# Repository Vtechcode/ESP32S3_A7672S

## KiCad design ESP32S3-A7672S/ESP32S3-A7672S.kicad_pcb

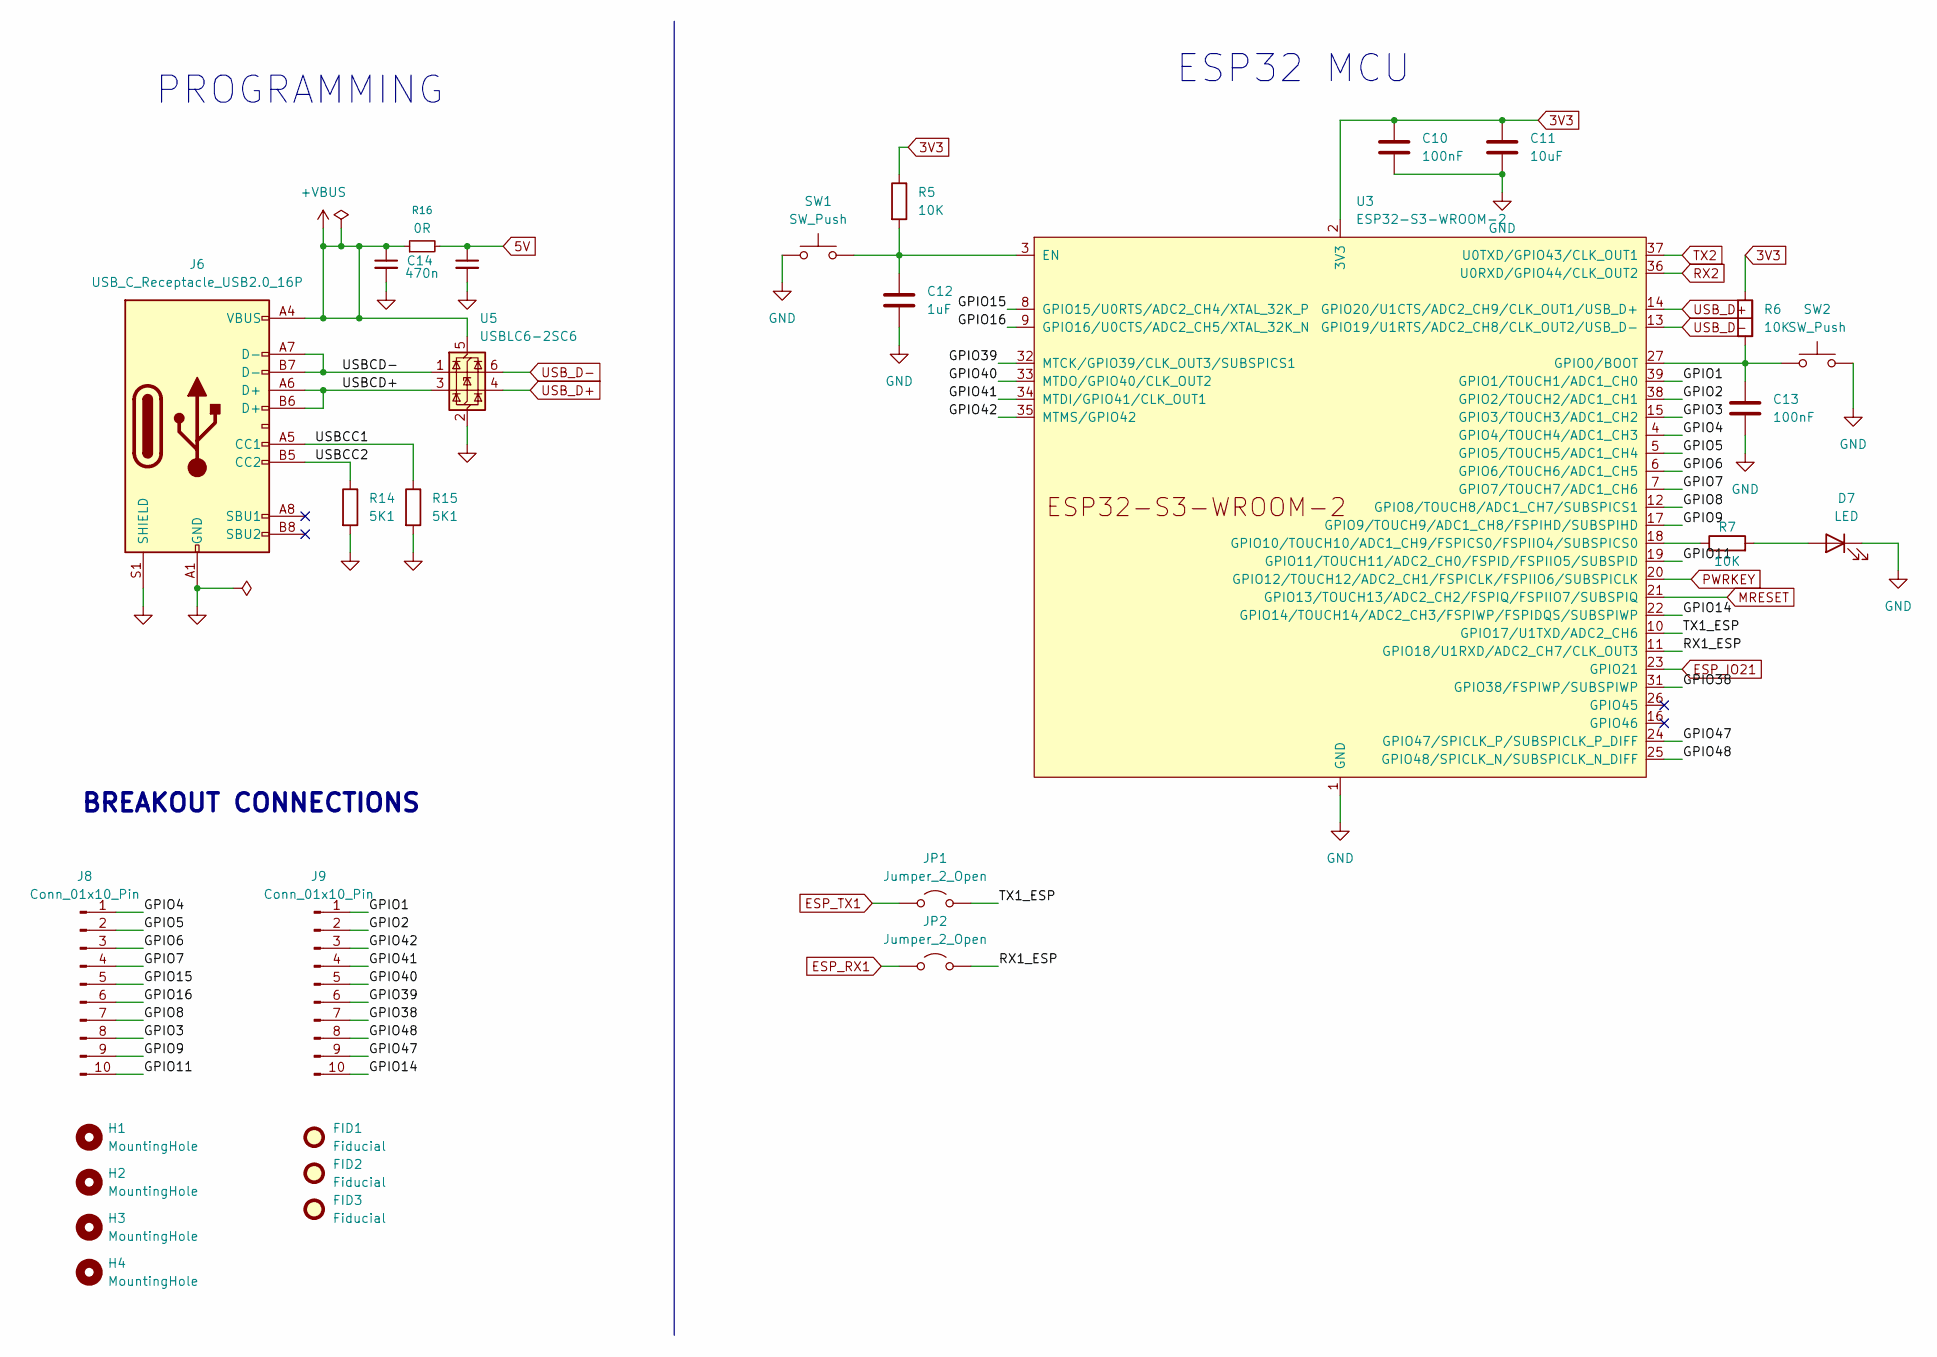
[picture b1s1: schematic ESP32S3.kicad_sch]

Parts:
C10, C13: 100nF; C_0603_1608Metric_Pad1.08x0.95mm_HandSolder; LCSC number C16194197
C11: 10uF; C_0603_1608Metric_Pad1.08x0.95mm_HandSolder; LCSC number C194427
C12: 1uF; C_0603_1608Metric_Pad1.08x0.95mm_HandSolder; LCSC number C29936
C14, C15: 470n; C_0402_1005Metric; LCSC number C364319
D7: LED; LED_0805_2012Metric_Pad1.15x1.40mm_HandSolder; LCSC number C5879383
FID1, FID2, FID3: Fiducial; Fiducial_0.5mm_Mask1.5mm
H1, H2, H3, H4: MountingHole; MountingHole_3.2mm_M3
J6: USB_C_Receptacle_USB2.0_16P; USB_C_Receptacle_GCT_USB4105-xx-A_16P_TopMnt_Horizontal; LCSC number C45082766
J8, J9: Conn_01x10_Pin; PinSocket_1x10_P2.54mm_Vertical
JP1, JP2: Jumper_2_Open; TestPoint_2Pads_Pitch2.54mm_Drill0.8mm
R5, R6, R7: 10K; R_0603_1608Metric_Pad0.98x0.95mm_HandSolder; LCSC number C2479067
R14: 5K1; R_0603_1608Metric_Pad0.98x0.95mm_HandSolder; LCSC number C123727
R15: 5K1; R_0402_1005Metric; LCSC number C123727
R16: 0R; R_0603_1608Metric; LCSC number C100044
SW1, SW2: SW_Push; SW_PUSH_6mm; LCSC number C428628
U3: ESP32-S3-WROOM-2; LCSC number C42417293
U5: USBLC6-2SC6; SOT-23-6; LCSC number C7519

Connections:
3V3: C10.1, C11.1, R5.1, R6.1, U3.2 (3V3); also elsewhere on the board
5V: C15.1, R16.2; also elsewhere on the board
+VBUS: C14.1, J6.A4 (VBUS), J6.A9 (VBUS), J6.B4 (VBUS), J6.B9 (VBUS), R16.1, U5.5 (VBUS)
/ESP32S3/GPIO1: J9.1, U3.39 (GPIO1/TOUCH1/ADC1_CH0)
/ESP32S3/GPIO2: J9.2, U3.38 (GPIO2/TOUCH2/ADC1_CH1)
/ESP32S3/GPIO3: J8.8, U3.15 (GPIO3/TOUCH3/ADC1_CH2)
/ESP32S3/GPIO4: J8.1, U3.4 (GPIO4/TOUCH4/ADC1_CH3)
/ESP32S3/GPIO5: J8.2, U3.5 (GPIO5/TOUCH5/ADC1_CH4)
/ESP32S3/GPIO6: J8.3, U3.6 (GPIO6/TOUCH6/ADC1_CH5)
/ESP32S3/GPIO7: J8.4, U3.7 (GPIO7/TOUCH7/ADC1_CH6)
/ESP32S3/GPIO8: J8.7, U3.12 (GPIO8/TOUCH8/ADC1_CH7/SUBSPICS1)
/ESP32S3/GPIO9: J8.9, U3.17 (GPIO9/TOUCH9/ADC1_CH8/FSPIHD/SUBSPIHD)
/ESP32S3/GPIO11: J8.10, U3.19 (GPIO11/TOUCH11/ADC2_CH0/FSPID/FSPIIO5/S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)
/ESP32S3/GPIO14: J9.10, U3.22 (GPIO14/TOUCH14/ADC2_CH3/FSPIWP/FSPIDQS/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)
/ESP32S3/GPIO15: J8.5, U3.8 (GPIO15/U0RTS/ADC2_CH4/XTAL_32K_P)
/ESP32S3/GPIO16: J8.6, U3.9 (GPIO16/U0CTS/ADC2_CH5/XTAL_32K_N)
/ESP32S3/GPIO38: J9.7, U3.31 (GPIO38/FSPIWP/SUBSPIWP)
/ESP32S3/GPIO39: J9.6, U3.32 (MTCK/GPIO39/CLK_OUT3/SUBSPICS1)
/ESP32S3/GPIO40: J9.5, U3.33 (MTDO/GPIO40/CLK_OUT2)
/ESP32S3/GPIO41: J9.4, U3.34 (MTDI/GPIO41/CLK_OUT1)
/ESP32S3/GPIO42: J9.3, U3.35 (MTMS/GPIO42)
/ESP32S3/GPIO47: J9.9, U3.24 (GPIO47/SPICLK_P/SUBSPICLK_P_DIFF)
/ESP32S3/GPIO48: J9.8, U3.25 (GPIO48/SPICLK_N/SUBSPICLK_N_DIFF)
/ESP32S3/RX1_ESP: JP2.2 (B), U3.11 (GPIO18/U1RXD/ADC2_CH7/CLK_OUT3)
/ESP32S3/TX1_ESP: JP1.2 (B), U3.10 (GPIO17/U1TXD/ADC2_CH6)
/ESP32S3/USBCC1: J6.A5 (CC1), R15.1
/ESP32S3/USBCC2: J6.B5 (CC2), R14.1
/ESP32S3/USBCD+: J6.A6 (D+), J6.B6 (D+), U5.3 (I/O2)
/ESP32S3/USBCD-: J6.A7 (D-), J6.B7 (D-), U5.1 (I/O1)
ESP_IO21: U3.23 (GPIO21); also elsewhere on the board
ESP_RX1: JP2.1 (A); also elsewhere on the board
ESP_TX1: JP1.1 (A); also elsewhere on the board
GND: C10.2, C11.2, C12.2, C13.2, C14.2, C15.2, D7.1 (K), J6.A1 (GND), J6.A12 (GND), J6.B1 (GND), J6.B12 (GND), J6.S1 (SHIELD), R14.2, R15.2, SW1.1, SW2.2, U3.1 (GND), U3.40 (GND), U3.41 (GND), U5.2 (GND); also elsewhere on the board
MRESET: U3.21 (GPIO13/TOUCH13/ADC2_CH2/FSPIQ/FSPIIO7/S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); also elsewhere on the board
unnamed: D7.2 (A), R7.2
unnamed: C12.1, R5.2, SW1.2, U3.3 (EN)
unnamed: C13.1, R6.2, SW2.1, U3.27 (GPIO0/BOOT)
unnamed: R7.1, U3.18 (GPIO10/TOUCH10/ADC1_CH9/FSPICS0/FSPIIO4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)
PWRKEY: U3.20 (GPIO12/TOUCH12/ADC2_CH1/FSPICLK/FSPIIO6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); also elsewhere on the board
RX2: U3.36 (U0RXD/GPIO44/CLK_OUT2); also elsewhere on the board
TX2: U3.37 (U0TXD/GPIO43/CLK_OUT1); also elsewhere on the board
USB_D+: U3.14 (GPIO20/U1CTS/ADC2_CH9/CLK_OUT1/USB_D+), U5.4 (I/O2)
USB_D-: U3.13 (GPIO19/U1RTS/ADC2_CH8/CLK_OUT2/USB_D-), U5.6 (I/O1)

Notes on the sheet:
ESP32 MCU
BREAKOUT CONNECTIONS
PROGRAMMING

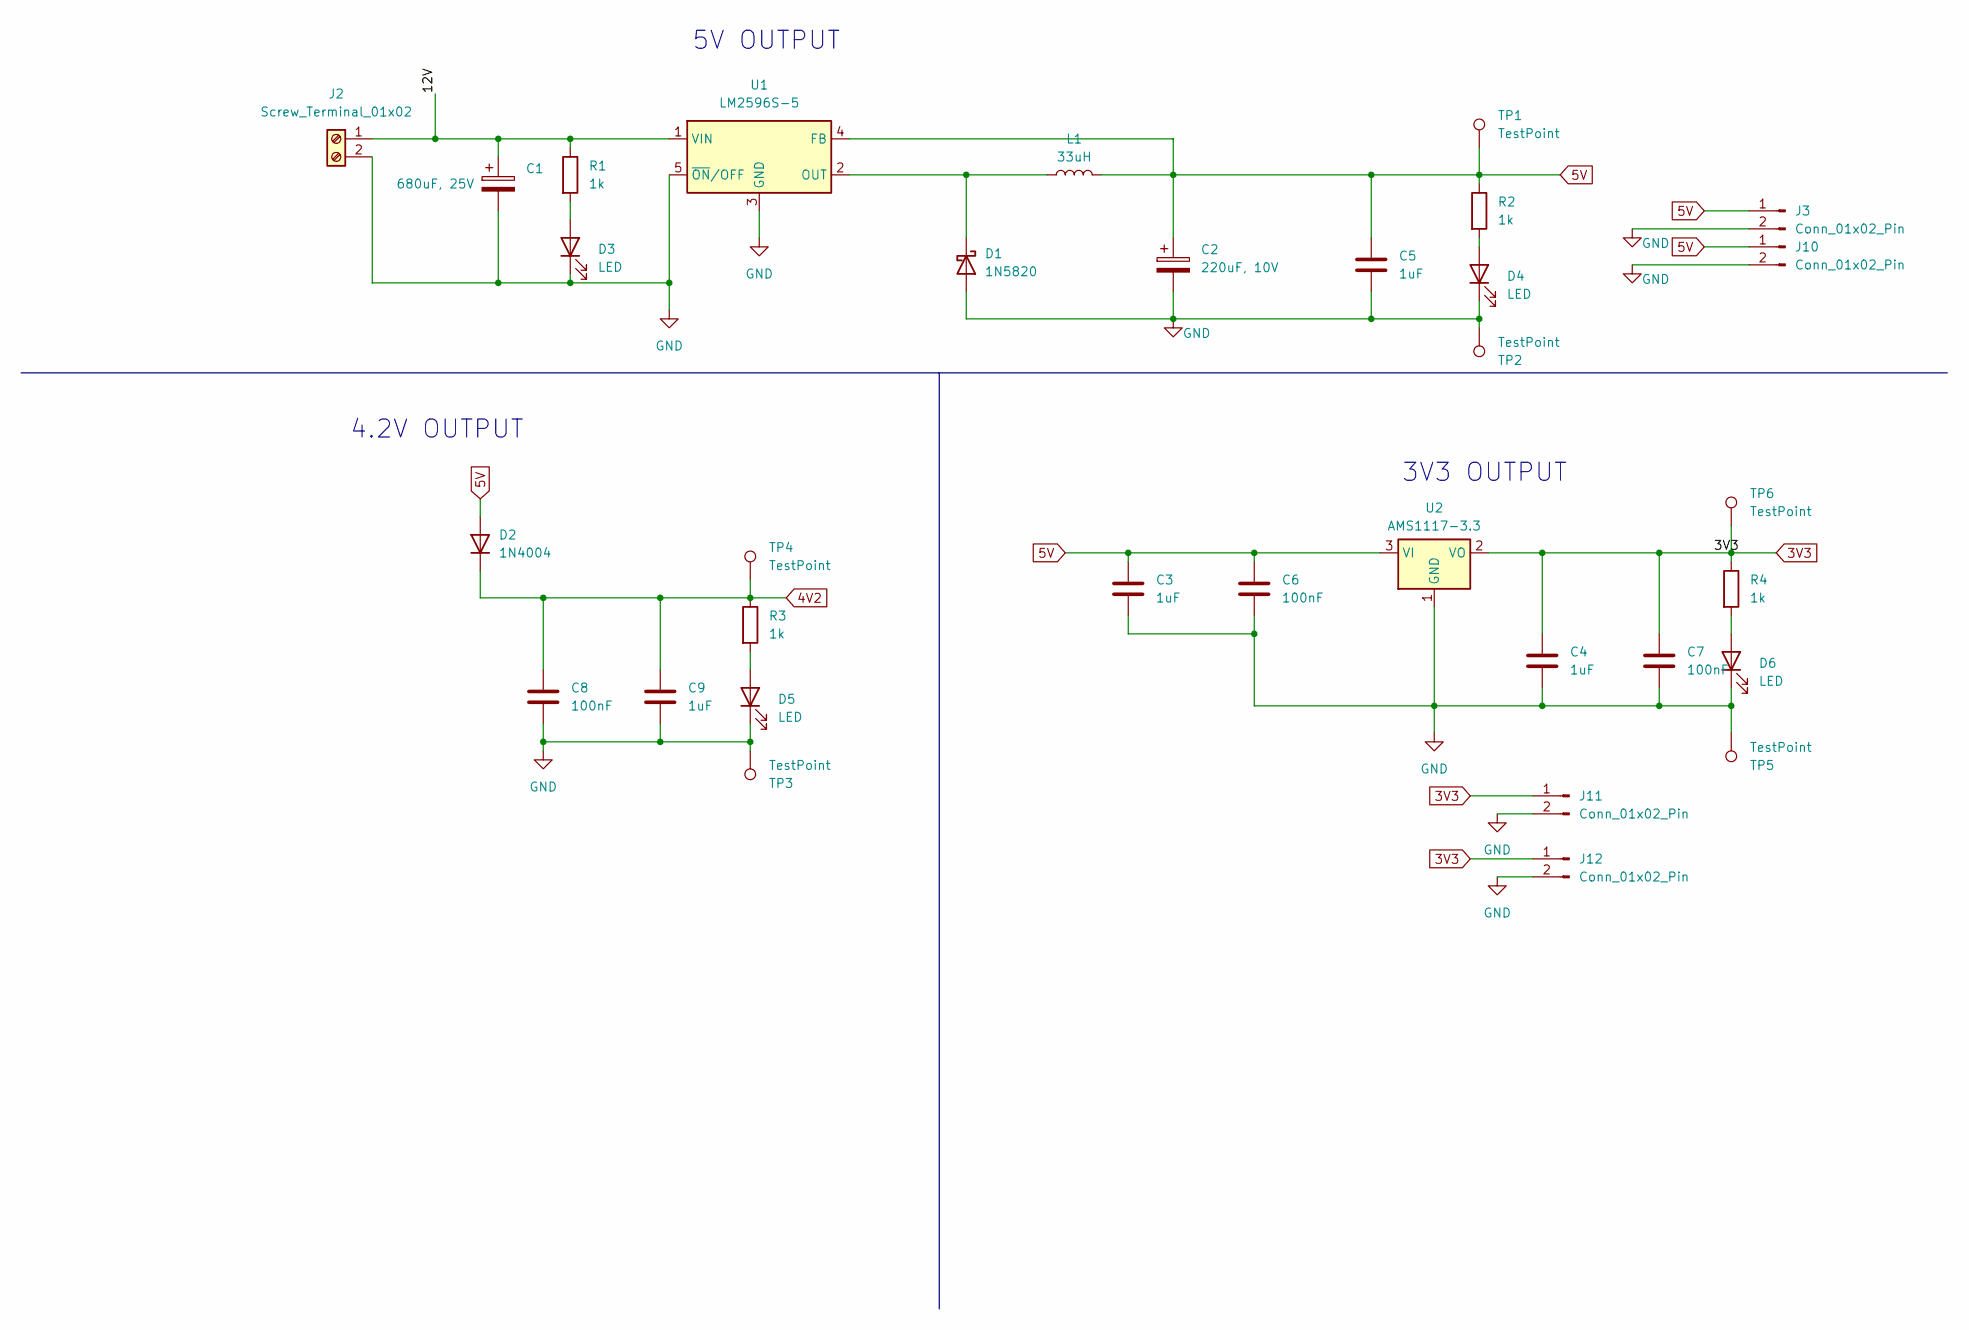
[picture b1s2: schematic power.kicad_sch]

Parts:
C1: 680uF, 25V; CP_Elec_10x7.7; LCSC number C494831
C2: 220uF, 10V; CP_Elec_6.3x7.7; LCSC number C336207
C3, C4, C5, C9: 1uF; C_0603_1608Metric_Pad1.08x0.95mm_HandSolder; LCSC number C29936
C6, C7, C8: 100nF; C_0603_1608Metric_Pad1.08x0.95mm_HandSolder; LCSC number C16194197
D1: 1N5820; D_SMA; LCSC number C95400
D2: 1N4004; D_SMA; LCSC number C727080
D3, D4, D5, D6: LED; LED_0805_2012Metric; LCSC number C5875730
J2: Screw_Terminal_01x02; TerminalBlock_Phoenix_MKDS-1,5-2-5.08_1x02_P5.08mm_Horizont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; LCSC number C5183929
J3, J10, J11, J12: Conn_01x02_Pin; PinHeader_1x02_P2.54mm_Vertical
L1: 33uH; L_Coilcraft_LPS4018; LCSC number C5350136
R1, R2, R3, R4: 1k; R_0603_1608Metric; LCSC number C860716
TP1, TP2, TP3, TP4, TP5, TP6: TestPoint; TestPoint_Pad_D2.0mm
U1: LM2596S-5; TO-263-5_TabPin3; LCSC number C116713
U2: AMS1117-3.3; SOT-223-3_TabPin2; LCSC number C9662

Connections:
3V3: C4.1, C7.1, J11.1, J12.1, R4.1, TP6.1, U2.2 (VO); also elsewhere on the board
4V2: C8.1, C9.1, D2.1 (K), R3.1, TP4.1; also elsewhere on the board
5V: C2.1, C3.1, C5.1, C6.1, D2.2 (A), J3.1, J10.1, L1.2, R2.1, TP1.1, U1.4 (FB), U2.3 (VI); also elsewhere on the board
/POWER/12V: C1.1, J2.1, R1.1, U1.1 (VIN)
GND: C1.2, C2.2, C3.2, C4.2, C5.2, C6.2, C7.2, C8.2, C9.2, D1.2 (A), D3.1 (K), D4.1 (K), D5.1 (K), D6.1 (K), J2.2, J3.2, J10.2, J11.2, J12.2, TP2.1, TP3.1, TP5.1, U1.3 (GND), U1.5 (~ON/OFF), U2.1 (GND); also elsewhere on the board
unnamed: D1.1 (K), L1.1, U1.2 (OUT)
unnamed: D3.2 (A), R1.2
unnamed: D4.2 (A), R2.2
unnamed: D5.2 (A), R3.2
unnamed: D6.2 (A), R4.2

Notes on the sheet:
3V3 OUTPUT
5V OUTPUT
4.2V OUTPUT

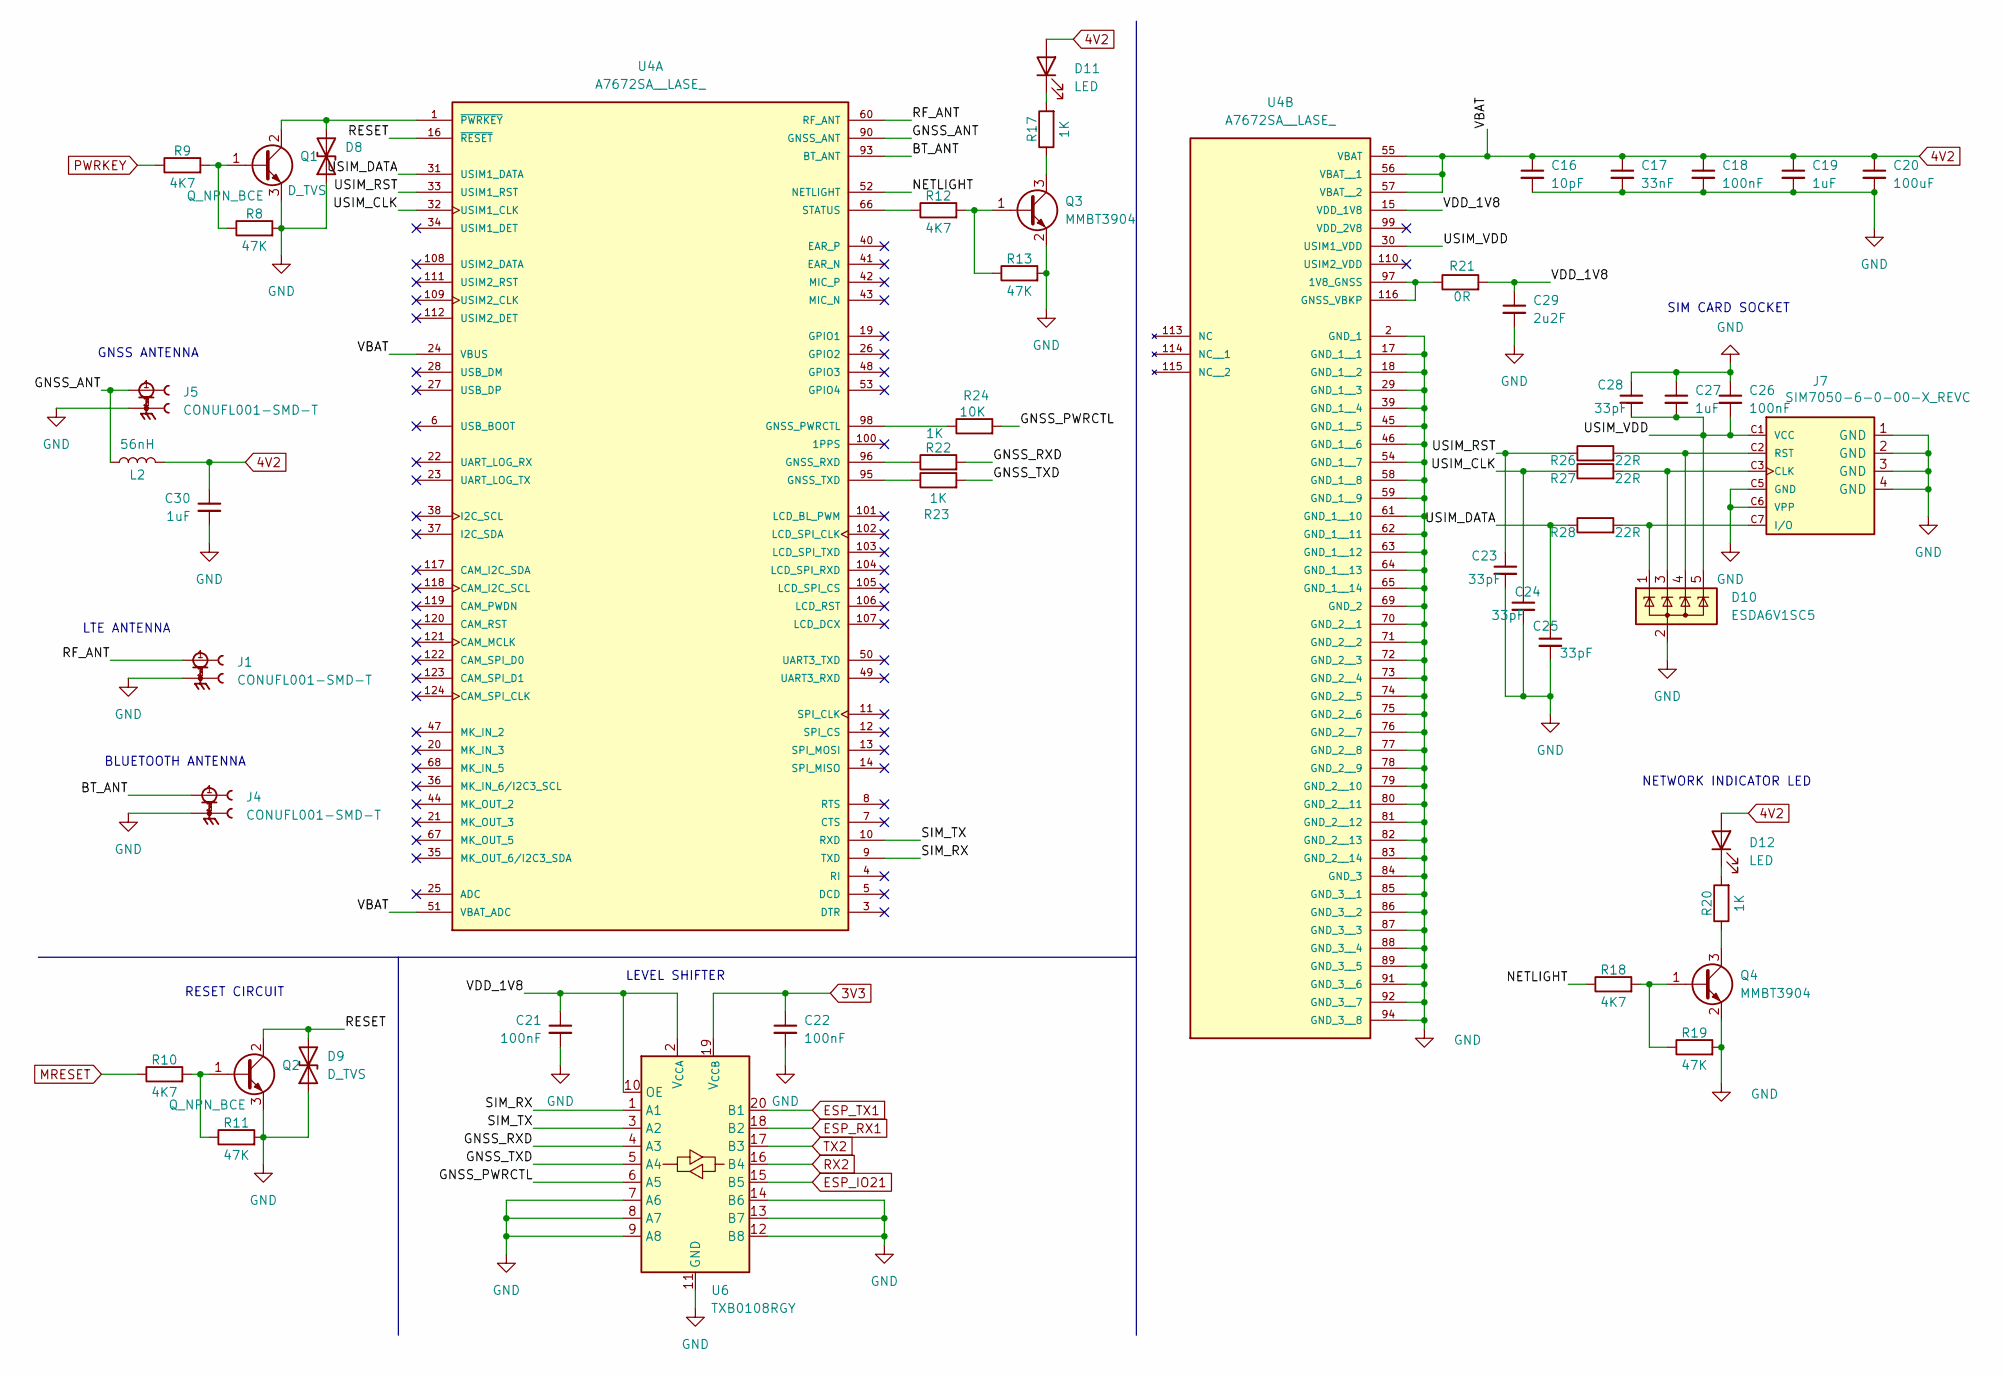
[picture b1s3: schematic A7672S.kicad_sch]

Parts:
C16: 10pF; C_0603_1608Metric_Pad1.08x0.95mm_HandSolder; LCSC number C2167326
C17: 33nF; C_0603_1608Metric_Pad1.08x0.95mm_HandSolder; LCSC number C16194260
C18: 100nF; C_0603_1608Metric_Pad1.08x0.95mm_HandSolder; LCSC number C16194197
C19: 1uF; C_0603_1608Metric_Pad1.08x0.95mm_HandSolder; LCSC number C29936
C20: 100uF; C_0805_2012Metric; LCSC number C141660
C21, C22, C26: 100nF; C_0603_1608Metric; LCSC number C16194197
C23, C24, C25, C28: 33pF; C_0603_1608Metric; LCSC number C1663
C27, C30: 1uF; C_0603_1608Metric; LCSC number C29936
C29: 2u2F; C_0603_1608Metric_Pad1.08x0.95mm_HandSolder; LCSC number C23630
D8, D9: D_TVS; D_SOD-923; LCSC number C87910
D10: ESDA6V1SC5; SOT-23-5; LCSC number C2935146
D11, D12: LED; LED_0805_2012Metric_Pad1.15x1.40mm_HandSolder; LCSC number C5879383
J1, J4, J5: CONUFL001-SMD-T; LINX_CONUFL001-SMD-T; LCSC number C22418213
J7: SIM7050-6-0-00-X_REVC; GCT_SIM7050-6-0-00-X_REVC; LCSC number C7363806
L2: 56nH; L_0603_1608Metric; LCSC number C98079
Q1, Q2: Q_NPN_BCE; SOT-23; LCSC number C513268
Q3, Q4: MMBT3904; SOT-23; LCSC number C81464
R8, R11, R13, R19: 47K; R_0603_1608Metric_Pad0.98x0.95mm_HandSolder; LCSC number C105579
R9, R10, R12, R18: 4K7; R_0603_1608Metric_Pad0.98x0.95mm_HandSolder; LCSC number C99782
R17, R20, R23: 1K; R_0603_1608Metric_Pad0.98x0.95mm_HandSolder; LCSC number C860716
R21: 0R; R_0805_2012Metric_Pad1.20x1.40mm_HandSolder; LCSC number C100045
R22: 1K; R_0603_1608Metric; LCSC number C98079
R24: 10K; R_0603_1608Metric_Pad0.98x0.95mm_HandSolder; LCSC number C2479067
R26, R27, R28: 22R; R_0603_1608Metric; LCSC number C2479410
U4: A7672SA__LASE_; XCVR_A7672SA__LASE_; PARTREV 1.03; LCSC number C5370391
U6: TXB0108RGY; Texas_RGY_R-PVQFN-N20_EP2.05x3.05mm; LCSC number C194701

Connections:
3V3: C22.1, U6.19 (V_{CCB}); also elsewhere on the board
4V2: C16.1, C17.1, C18.1, C19.1, C20.1, C30.1, D11.2 (A), D12.2 (A), L2.2, U4.24 (VBUS), U4.51 (VBAT_ADC), U4.55 (VBAT), U4.56 (VBAT__1), U4.57 (VBAT__2); also elsewhere on the board
/A7672S/BT_ANT: J4.1, U4.93 (BT_ANT)
/A7672S/GNSS_ANT: J5.1, L2.1, U4.90 (GNSS_ANT)
/A7672S/GNSS_PWRCTL: R24.2, U6.6 (A5)
/A7672S/GNSS_RXD: R22.2, U6.4 (A3)
/A7672S/GNSS_TXD: R23.2, U6.5 (A4)
/A7672S/NETLIGHT: R18.1, U4.52 (NETLIGHT)
/A7672S/RESET: D9.2 (A2), Q2.2 (C), U4.16 (~RESET)
/A7672S/RF_ANT: J1.1, U4.60 (RF_ANT)
/A7672S/SIM_RX: U4.9 (TXD), U6.1 (A1)
/A7672S/SIM_TX: U4.10 (RXD), U6.3 (A2)
/A7672S/USIM_CLK: C24.1, R27.1, U4.32 (USIM1_CLK)
/A7672S/USIM_DATA: C25.1, R28.1, U4.31 (USIM1_DATA)
/A7672S/USIM_RST: C23.1, R26.1, U4.33 (USIM1_RST)
/A7672S/USIM_VDD: C26.2, C27.2, C28.2, D10.5 (K), J7.C1 (VCC), U4.30 (USIM1_VDD)
/A7672S/VDD_1V8: C21.1, C29.1, R21.2, U4.15 (VDD_1V8), U6.2 (V_{CCA}), U6.10 (OE)
ESP_IO21: U6.15 (B5); also elsewhere on the board
ESP_RX1: U6.18 (B2); also elsewhere on the board
ESP_TX1: U6.20 (B1); also elsewhere on the board
GND: C16.2, C17.2, C18.2, C19.2, C20.2, C21.2, C22.2, C23.2, C24.2, C25.2, C26.1, C27.1, C28.1, C29.2, C30.2, D8.1 (A1), D9.1 (A1), D10.2 (A), J1.2, J1.3, J4.2, J4.3, J5.2, J5.3, J7.1 (GND), J7.2 (GND), J7.3 (GND), J7.4 (GND), J7.C5 (GND), J7.C6 (VPP), Q1.3 (E), Q2.3 (E), Q3.2 (E), Q4.2 (E), R8.2, R11.2, R13.2, R19.2, U4.2 (GND_1), U4.17 (GND_1__1), U4.18 (GND_1__2), U4.29 (GND_1__3), U4.39 (GND_1__4), U4.45 (GND_1__5), U4.46 (GND_1__6), U4.54 (GND_1__7), U4.58 (GND_1__8), U4.59 (GND_1__9), U4.61 (GND_1__10), U4.62 (GND_1__11), U4.63 (GND_1__12), U4.64 (GND_1__13), U4.65 (GND_1__14), U4.69 (GND_2), U4.70 (GND_2__1), U4.71 (GND_2__2), U4.72 (GND_2__3), U4.73 (GND_2__4), U4.74 (GND_2__5), U4.75 (GND_2__6), U4.76 (GND_2__7), U4.77 (GND_2__8), U4.78 (GND_2__9), U4.79 (GND_2__10), U4.80 (GND_2__11), U4.81 (GND_2__12), U4.82 (GND_2__13), U4.83 (GND_2__14), U4.84 (GND_3), U4.85 (GND_3__1), U4.86 (GND_3__2), U4.87 (GND_3__3), U4.88 (GND_3__4), U4.89 (GND_3__5), U4.91 (GND_3__6), U4.92 (GND_3__7), U4.94 (GND_3__8), U6.7 (A6), U6.8 (A7), U6.9 (A8), U6.11 (GND), U6.12 (B8), U6.13 (B7), U6.14 (B6), U6.21 (GND); also elsewhere on the board
MRESET: R10.1; also elsewhere on the board
unnamed: D8.2 (A2), Q1.2 (C), U4.1 (~PWRKEY)
unnamed: D11.1 (K), R17.2
unnamed: D12.1 (K), R20.2
unnamed: D10.3 (K), J7.C3 (CLK), R27.2
unnamed: D10.1 (K), J7.C7 (I/O), R28.2
unnamed: D10.4 (K), J7.C2 (RST), R26.2
unnamed: Q1.1 (B), R8.1, R9.2
unnamed: Q2.1 (B), R10.2, R11.1
unnamed: Q3.1 (B), R12.2, R13.1
unnamed: Q3.3 (C), R17.1
unnamed: Q4.1 (B), R18.2, R19.1
unnamed: Q4.3 (C), R20.1
unnamed: R24.1, U4.98 (GNSS_PWRCTL)
unnamed: R22.1, U4.96 (GNSS_RXD)
unnamed: R23.1, U4.95 (GNSS_TXD)
unnamed: R12.1, U4.66 (STATUS)
unnamed: R21.1, U4.97 (1V8_GNSS), U4.116 (GNSS_VBKP)
PWRKEY: R9.1; also elsewhere on the board
RX2: U6.16 (B4); also elsewhere on the board
TX2: U6.17 (B3); also elsewhere on the board

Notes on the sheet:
BLUETOOTH ANTENNA
GNSS ANTENNA
LEVEL SHIFTER
SIM CARD SOCKET
RESET CIRCUIT
LTE ANTENNA
NETWORK INDICATOR LED

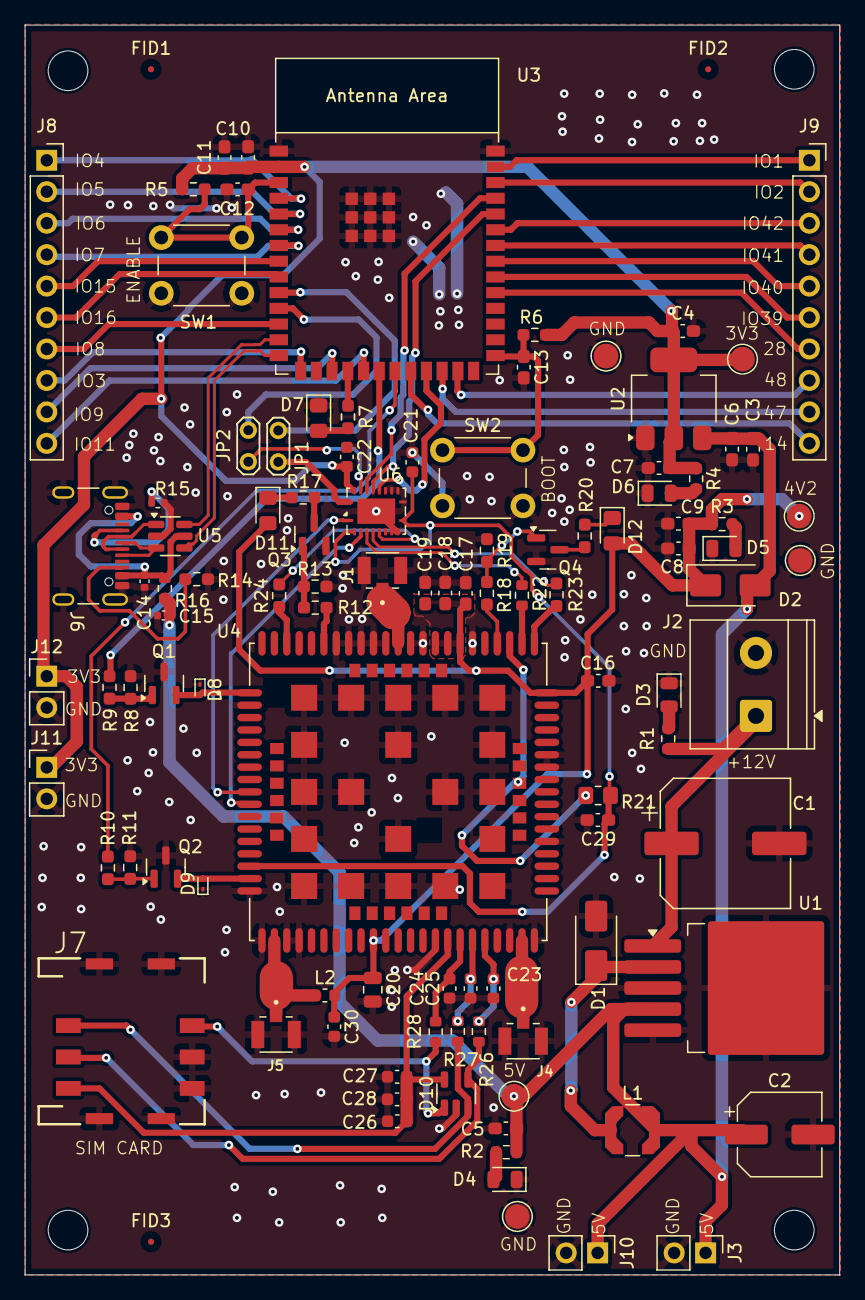
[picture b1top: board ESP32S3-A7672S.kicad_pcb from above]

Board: 2 copper layers, 65.8 x 100.9 mm, 110 parts (0 on the bottom side), 82 nets.
